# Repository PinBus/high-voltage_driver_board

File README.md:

# High Voltage Driver Board - Rev. 1.0

This board has four independant high voltage drivers. These boards were designed to drive pinball machine solenoids, but their use is not limited to pinball machines. These boards can als be used to drive high power LEDs, DC motors, etc... As long as the used [IRL540](assets/irl540.pdf) MOSFETs are able to provide enough power to the device being driven. The MOSFETs are driven by the [PC817](assets/pc817.pdf) opto-couplers, so the digital inputs are isolated from the high-power section.

The outputs can be configured in two ways. Every output can be exposed by a separate 2-pin connector, or two outputs can be joined together into a 3-pin connector. This is useful for flipper solenoids.

Pin 1 (marked by the square footprint) on J1 is the common ground pin. Pin 1 on jumper J2 is +5V, pin 2 is ground, and pin 3 is +25V to max. +75V.

**Warning: These designs are made as part of a hobby project and thus come with no guarantees. Do not use these designs in for any critical systems! Working with voltages higher than +40V can be potentially dangerous, please take appropriate safety measures!**

## BOM

| Identifiers | Quantity | Part |
| ----------- | -------- | ---- |
| D1          |       1x | 5mm red LED |
| D2 - D5     |       4x | 1N4004 compatible diode |
| J1          |       1x | JST XH connector, 2.5mm pitch, 5-way, through-hole |
| J2          |       1x | CH 3.96 connector, 3-way, through hole |
| J3 - J6     |          | CH 3.96 connector, 2x 3-way or 4x 2-way, through-hole |
| Q1 - Q4     |       4x | IRL540 MOSFET |
| R1 - R4     |       4x | 51Ω 0.25W resistor |
| R5          |       1x | 470Ω 0.25W resistor |
| R6 - R9     |       4x | 1kΩ 0.25W resistor |
| U1 - U4     |       4x | PC817 Sharp opto-coupler |

## Pictures

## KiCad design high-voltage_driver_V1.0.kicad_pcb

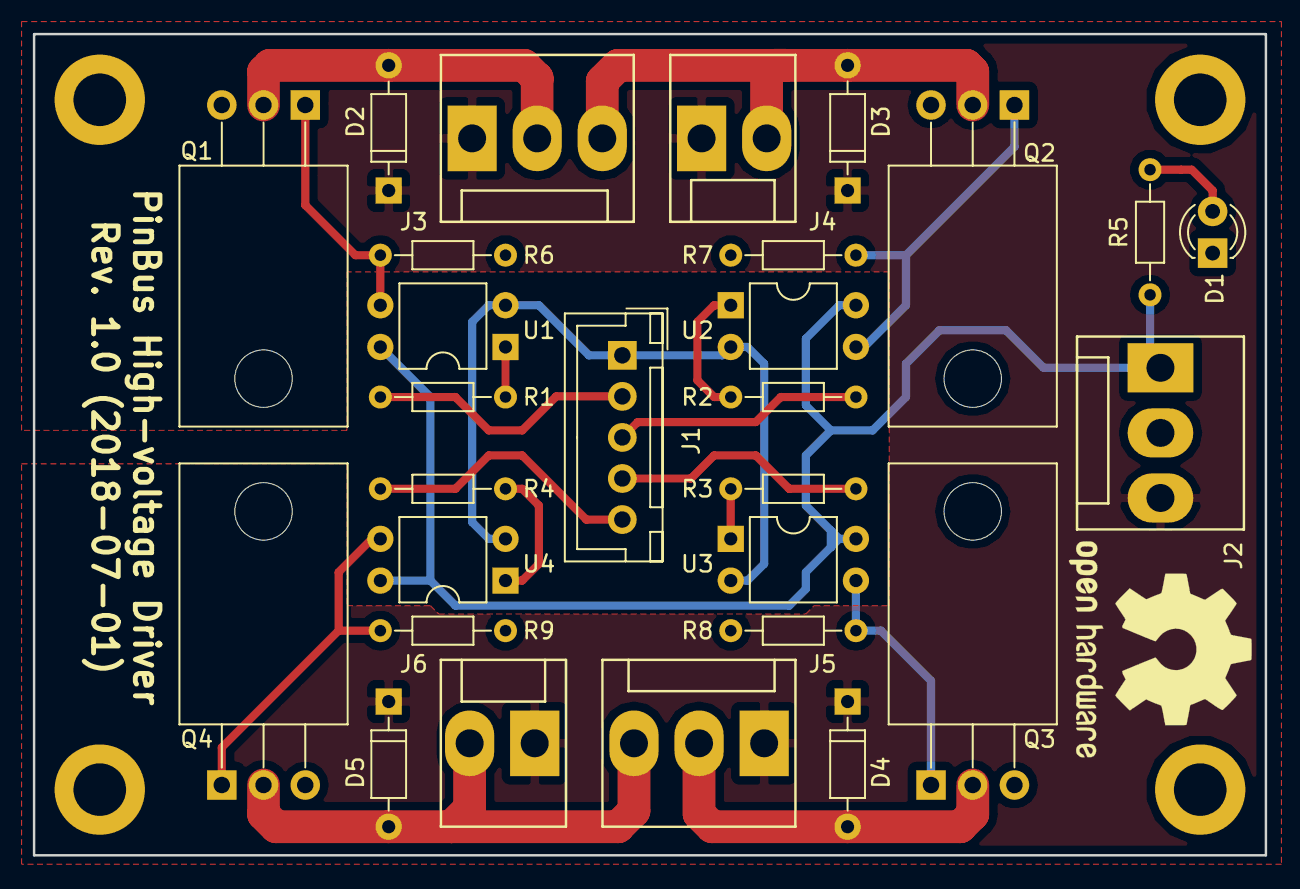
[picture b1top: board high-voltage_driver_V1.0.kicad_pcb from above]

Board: 2 copper layers, 75.0 x 50.0 mm, 28 parts (0 on the bottom side), 21 nets.

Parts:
D1: LED; LED_D3.0mm
D2, D3, D4, D5: D; D_DO-35_SOD27_P7.62mm_Horizontal
J1: CONN_01X05; JST_XH_B05B-XH-A_05x2.50mm_Straight
J2, J3, J5: CONN_01X03; Molex_KK-41791-03_03x3.96mm_Straight
J4, J6: CONN_01X02; Molex_KK-41791-02_02x3.96mm_Straight
Q1, Q2, Q3, Q4: Q_NMOS_DSG; TO-220-3_Horizontal
R1, R2, R3, R4: 51R; R_Axial_DIN0204_L3.6mm_D1.6mm_P7.62mm_Horizontal
R5: 470; R_Axial_DIN0204_L3.6mm_D1.6mm_P7.62mm_Horizontal
R6, R7, R8, R9: 1K; R_Axial_DIN0204_L3.6mm_D1.6mm_P7.62mm_Horizontal
U1, U2, U3, U4: PC817; DIP-4_W7.62mm

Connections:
unnamed: D1.1, J2.2, Q1.3, Q2.3, Q3.3, Q4.3, R6.1, R7.1, R8.1, R9.1
unnamed: D1.2, R5.1
unnamed: D2.1, D3.1, D4.1, D5.1, J2.3, J3.1, J4.1, J5.1, J6.1
unnamed: D2.2, J3.2, Q1.2
unnamed: D3.2, J3.3, J4.2, Q2.2
unnamed: D4.2, J5.2, Q3.2
unnamed: D5.2, J5.3, J6.2, Q4.2
unnamed: J1.1, U1.2, U2.2, U3.2, U4.2
unnamed: J1.2, R1.2
unnamed: J1.3, R2.2
unnamed: J1.4, R3.2
unnamed: J1.5, R4.2
unnamed: J2.1, R5.2, U1.4, U2.4, U3.4, U4.4
unnamed: Q1.1, R6.2, U1.3
unnamed: Q2.1, R7.2, U2.3
unnamed: Q3.1, R8.2, U3.3
unnamed: Q4.1, R9.2, U4.3
unnamed: R1.1, U1.1
unnamed: R2.1, U2.1
unnamed: R3.1, U3.1
unnamed: R4.1, U4.1

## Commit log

2018-12-14 Add hardware design files
2019-01-17 Improve documentation
